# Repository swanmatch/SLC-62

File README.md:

# SLC-62
MicroPad Keyboard. Streaming Live Controller type 62.

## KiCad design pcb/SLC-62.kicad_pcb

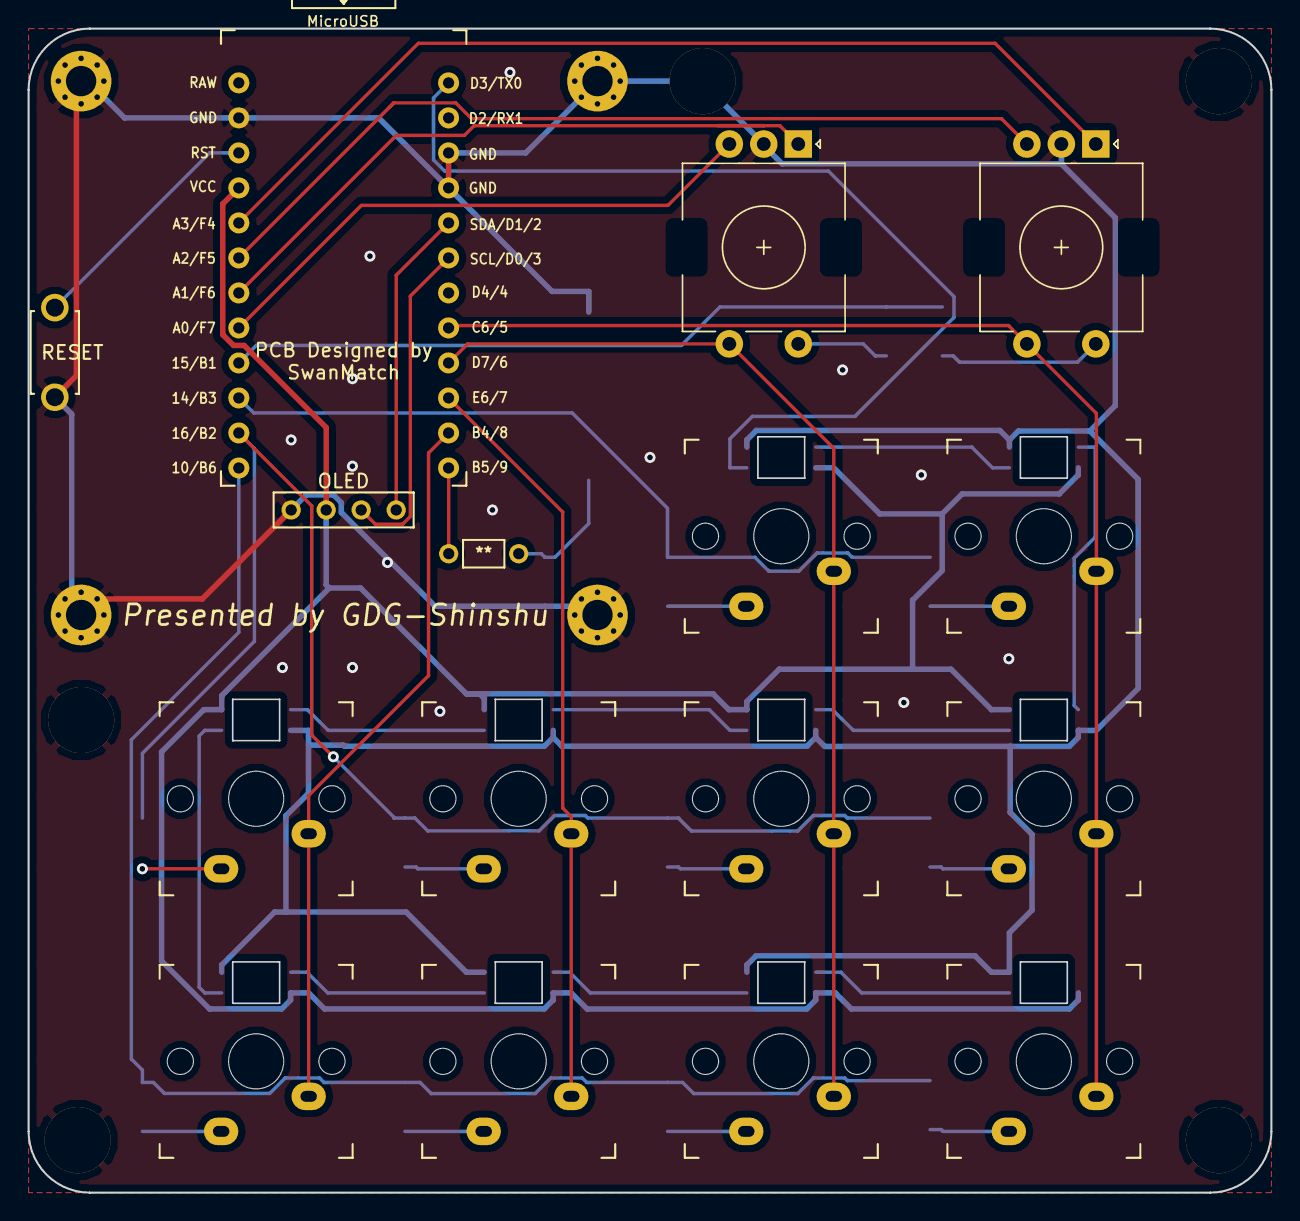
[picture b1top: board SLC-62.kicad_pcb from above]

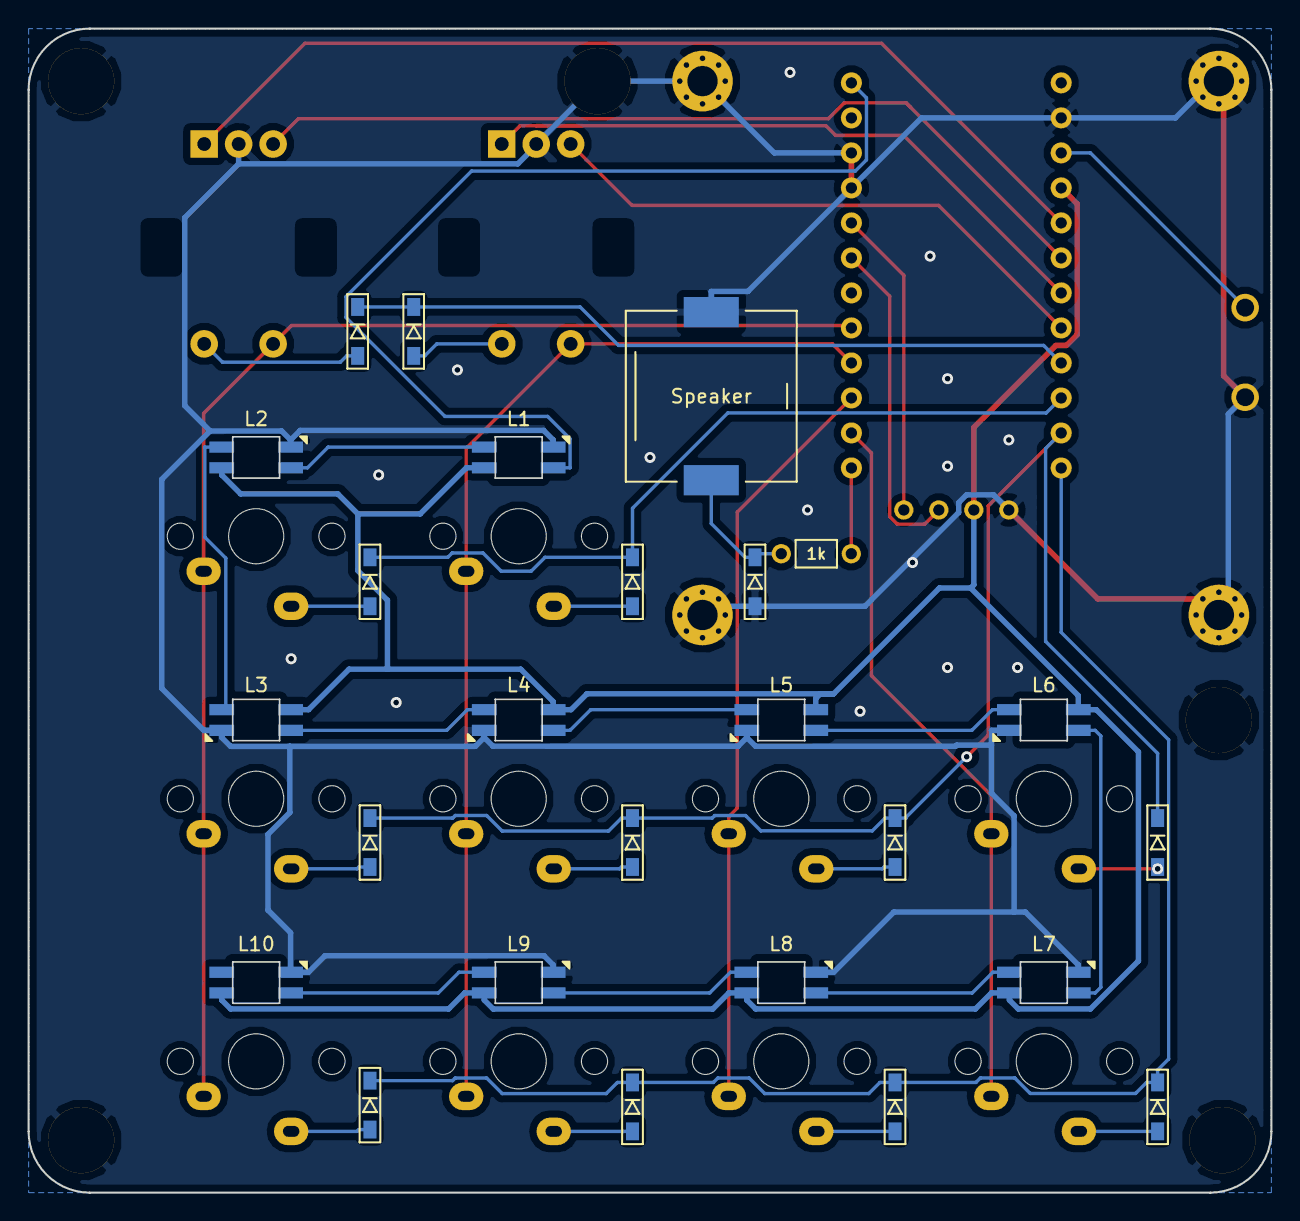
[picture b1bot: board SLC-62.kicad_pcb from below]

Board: 2 copper layers, 90.2 x 84.5 mm, 49 parts (25 on the bottom side), 41 nets.

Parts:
1k: 1k; R
D1, D2, D3, D4, D5, D6, D7, D8, D9, D10, D11, D12, D17: D; D3_SMD
J1: Conn_01x04; OLED_1side
J2, J3, J4, J5, J6: Conn_01x01; SpacerHole
J7, J8, J9, J10: Conn_01x01; MountingHole_2.2mm_M2_Pad_Via
L1, L2, L3, L4, L5, L6, L7, L8, L9, L10: YS-SK6812MINI; YS-SK6812MINI-E
SW1, SW2: Rotary_Encoder_Switch; RotaryEncoder_EC11
SW3, SW4, SW5, SW6, SW7, SW8, SW9, SW10, SW11, SW12: SW_PUSH; MX_1u
SW17: SW_PUSH; ResetSW_1side
Speaker: Speaker; PKLCS1212E4001_HandSoldering
U1: ProMicro; ProMicro_v3.5

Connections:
A1: SW1.A, U1.18
A2: SW2.A, U1.20
AUDIO: 1k.2, U1.12
B1: SW1.B, U1.17
B2: SW2.B, U1.19
COL1: SW5.1, SW9.1, U1.11
COL2: SW6.1, SW10.1, U1.10
COL3: SW1.S1, SW3.1, SW7.1, SW11.1, U1.9
COL4: SW2.S1, SW4.1, SW8.1, SW12.1, U1.8
GND: D17.2, J1.1, J2.1, J3.1, J4.1, J5.1, J6.1, J7.1, J8.1, J9.1, J10.1, L1.3, L2.3, L3.3, L4.3, L5.3, L6.3, L7.3, L8.3, L9.3, L10.3, SW1.C, SW2.C, SW17.2, Speaker.2, U1.3, U1.4, U1.23
LED: L1.4, U1.1
unnamed: D1.2, SW1.S2
unnamed: D2.2, SW2.S2
unnamed: D3.2, SW3.2
unnamed: D4.2, SW4.2
unnamed: D5.2, SW5.2
unnamed: D6.2, SW6.2
unnamed: D7.2, SW7.2
unnamed: D8.2, SW8.2
unnamed: D9.2, SW9.2
unnamed: D10.2, SW10.2
unnamed: D11.2, SW11.2
unnamed: D12.2, SW12.2
unnamed: 1k.1, D17.1, Speaker.1
unnamed: L1.2, L2.4
unnamed: L2.2, L3.4
unnamed: L3.2, L4.4
unnamed: L4.2, L5.4
unnamed: L5.2, L6.4
unnamed: L6.2, L7.4
unnamed: L7.2, L8.4
unnamed: L8.2, L9.4
unnamed: L9.2, L10.4
RESET: SW17.1, U1.22
ROW1: D1.1, D2.1, U1.16
ROW2: D3.1, D4.1, U1.15
ROW3: D5.1, D6.1, D7.1, D8.1, U1.14
ROW4: D9.1, D10.1, D11.1, D12.1, U1.13
SCL: J1.3, U1.6
SDA: J1.4, U1.5
VCC: J1.2, L1.1, L2.1, L3.1, L4.1, L5.1, L6.1, L7.1, L8.1, L9.1, L10.1, U1.21
